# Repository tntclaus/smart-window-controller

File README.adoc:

# Контроллер умного окна

[.float-group]
--
image::docs/3d.png[float=left,width=200pt]

Устройство для управления рулонной шторой. Умеет:

1. Прятаться внутри трубы рулонной шторы. Ставится с другого конца от механической крутилки и имеет такой же габарит. Механическая крутилка сохраняется т.к. вручную шторами тоже удобно управлять.
2. Двигать шторой, в том числе зеброй.
3. Датчиком освещенности следить, чтобы шторы пропускали необходимое количество света.может делиться этой инфой с другими шторами.
4. Датчиком холла контролить текущее положение шторы, даже если шторой управляют вручную через цепочку.
5. Автокалибровать положения полностью свернутой шторы концевиком если пропало электричество и штору двигали вручную.
6. Общаться с дополнительной переферией по i2c / uart (если есть).
7. Опрашивать датчик открытого окна (если есть).
--

## Печатные платы

Дизайн в kicad. Печатная плата распаивается непосредственно на двигатель.

[.float-group]
--
image::docs/top.png[float=left,width=300pt]
image::docs/bottom.png[float=left,width=300pt]
--

## Корпус и другие детали

Печатается на 3D принтере. Дизайн в openscad. Часть деталей предназначена для стыковки вала двигателя с трубой
для рулонных штор ø32мм, остальная часть — для крепления двигателя и печатной платы к окну/стене/раме.

Список деталей:

. Чехол для стыковки вала и трубы 32мм;
. Корпус контроллера с хомутным соединением с корпусом двигателя и винтовым с печатной платой;
. Кронштейн для крепления к окну конца трубы с двигателем;
. Звездочка для шариковой цепи с креплением к 32мм трубе;
. Кронштейн для крепления к окну конца трубы со звездочкой.

## Покупные компоненты

. Ткань для рулонной шторы;
. Труба для рулонных штор ø32мм;
. Двигатель с редуктором JGA25-370;
. Блок питания AC 220 -> 12V для питания двигателя;
. Полномостовой драйвер A4950;
. DC-DC преобразователь 5-25V -> 3.3V;
. ESP8266-12E / ESP8266-12F;
. (опция) SMD или DIP фоторезистор (LDR) — для них на плате предусмотрено 2 места. Можно сделать выносным.
. (опция) концевой выключатель — подключается через JST-PH (2мм шаг) разъём. Open drain.
. (опция) датчик открытия окна — подключается через JST-PH (2мм шаг) разъём. Open drain.
. (опция) I2C периферия — подключается через JST-EH (2.5мм шаг) разъём. Питание 3.3В.
. (опция) UART периферия — подключается через JST-EH (2.5мм шаг) разъём программирования. Питание нужно брать от разъёма I2C.

## Выбор двигателя

На 100-200 оборотов в минуту. Большее число оборотов теоретически может не дать нужного крутящего момента, меньшее число оборотов может сделать ручное раскручивание шторы проблематичным. Крутящий момент при 100 оборотах в минуту у большинства двигателей будет порядка 1 кг для барабана шторы с радиусом 2 см.

## Прошивка

Открытая прошивка ESPHome. Плата имеет разъёмы для загрузки собственной прошивки.

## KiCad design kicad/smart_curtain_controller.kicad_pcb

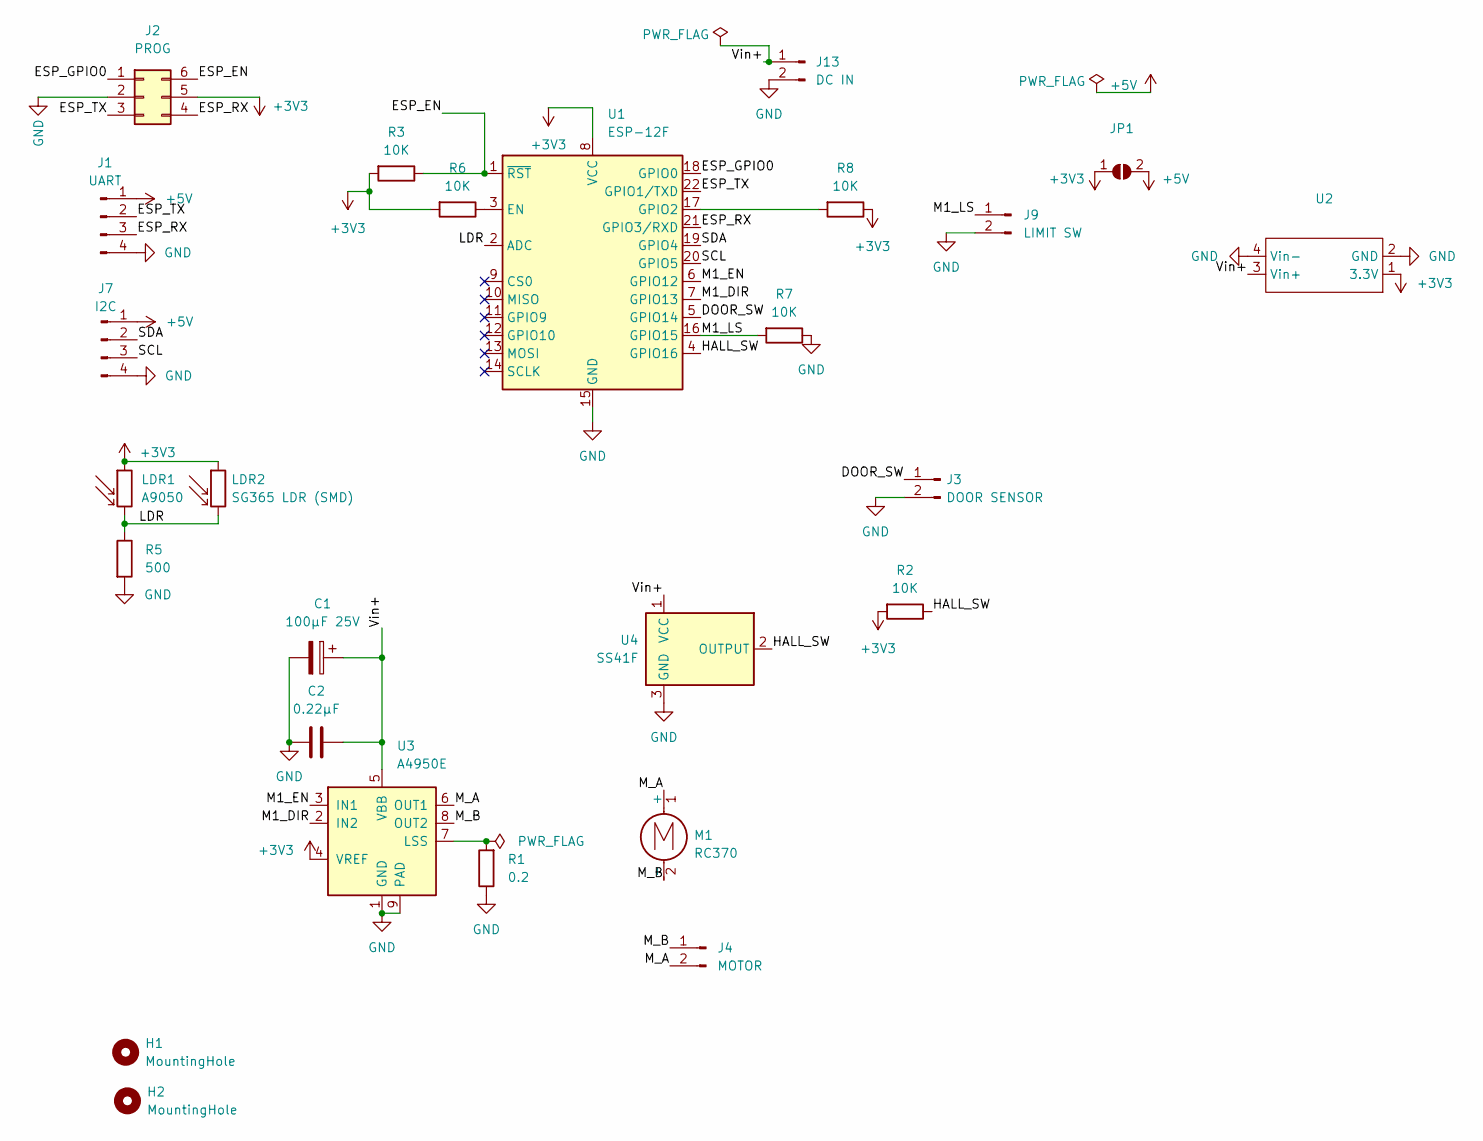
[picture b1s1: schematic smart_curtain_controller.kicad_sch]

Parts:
C1: 100µF 25V; CP_Radial_D6.3mm_P2.50mm
C2: 0.22µF; C_1206_3216Metric
H1, H2: MountingHole; MountingHole_3.2mm_M3
J1: UART; JST_PH_S4B-PH-K_1x04_P2.00mm_Horizontal
J2: PROG; PinHeader_2x03_P2.54mm_Vertical
J3: DOOR SENSOR; JST_PH_S2B-PH-K_1x02_P2.00mm_Horizontal
J4: MOTOR; JST_PH_S2B-PH-K_1x02_P2.00mm_Horizontal
J7: I2C; JST_PH_S4B-PH-K_1x04_P2.00mm_Horizontal
J9: LIMIT SW; JST_PH_S2B-PH-K_1x02_P2.00mm_Horizontal
J13: DC IN; JST_PH_S2B-PH-K_1x02_P2.00mm_Horizontal
JP1: (no value)
LDR1: A9050; R_LDR_5.0x4.1mm_P3mm_Vertical
LDR2: SG365 LDR (SMD); R_1210_3225Metric
M1: RC370
R1: 0.2; R_1206_3216Metric
R2, R3, R6, R7, R8: 10K; R_1206_3216Metric
R5: 500; R_1206_3216Metric
U1: ESP-12F; ESP-12E
U2: (no value)
U3: A4950E; SOIC-8-1EP_3.9x4.9mm_P1.27mm_EP2.41x3.3mm
U4: SS41F; Hall_Switch_TO-92

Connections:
+3V3: J2.5, JP1.1 (A), LDR1.1, LDR2.1, R2.2, R3.2, R6.2, R8.1, U1.8 (VCC), U2.1 (3.3V), U3.4 (VREF)
+5V: J1.1, J7.1, JP1.2 (B)
/DOOR_SW: J3.1, U1.5 (GPIO14)
/ESP_EN: J2.6, R3.1, U1.1 (~RST)
/ESP_GPIO0: J2.1, U1.18 (GPIO0)
/ESP_RX: J1.3, J2.4, U1.21 (GPIO3/RXD)
/ESP_TX: J1.2, J2.3, U1.22 (GPIO1/TXD)
/HALL_SW: R2.1, U1.4 (GPIO16), U4.2 (OUTPUT)
/LDR: LDR1.2, LDR2.2, R5.1, U1.2 (ADC)
/M1_DIR: U1.7 (GPIO13), U3.2 (IN2)
/M1_EN: U1.6 (GPIO12), U3.3 (IN1)
/M1_LS: J9.1, R7.2, U1.16 (GPIO15)
/M_A: J4.2, M1.1 (+), U3.6 (OUT1)
/M_B: J4.1, M1.2 (-), U3.8 (OUT2)
/SCL: J7.3, U1.20 (GPIO5)
/SDA: J7.2, U1.19 (GPIO4)
/Vin+: C1.1, C2.2, J13.1, U2.3 (Vin+), U3.5 (VBB), U4.1 (VCC)
GND: C1.2, C2.1, J1.4, J2.2, J3.2, J7.4, J9.2, J13.2, R1.1, R5.2, R7.1, U1.15 (GND), U2.2 (GND), U2.4 (Vin-), U3.1 (GND), U3.9 (PAD), U4.3 (GND)
unnamed: R1.2, U3.7 (LSS)
unnamed: R6.1, U1.3 (EN)
unnamed: R8.2, U1.17 (GPIO2)

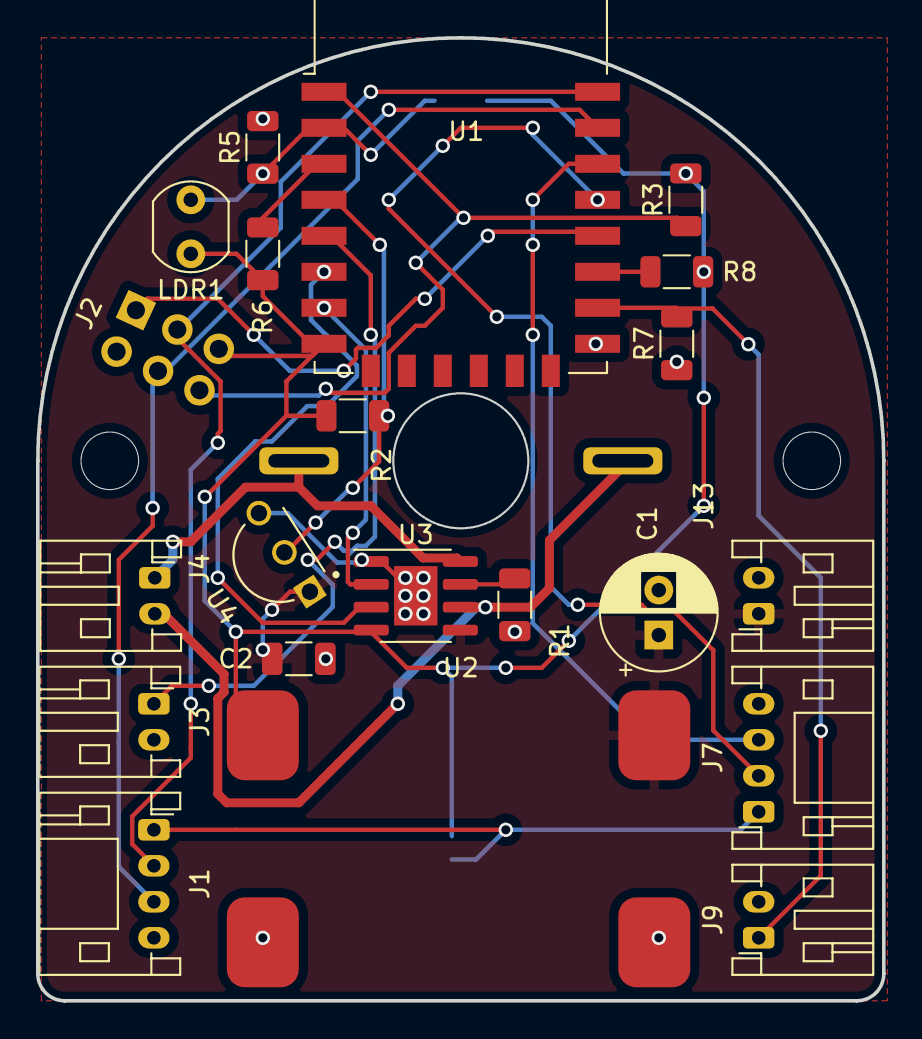
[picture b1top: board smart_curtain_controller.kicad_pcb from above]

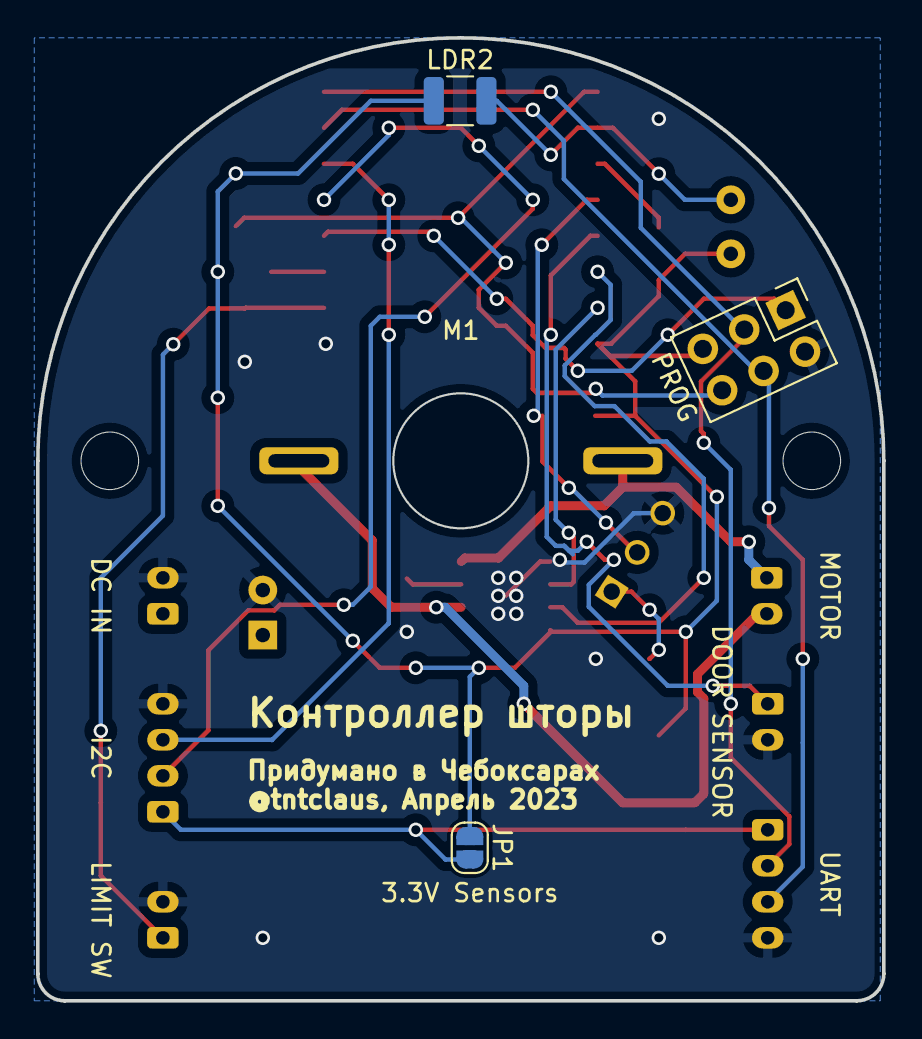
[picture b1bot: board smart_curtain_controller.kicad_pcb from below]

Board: 2 copper layers, 47.0 x 53.5 mm, 26 parts (4 on the bottom side), 21 nets.

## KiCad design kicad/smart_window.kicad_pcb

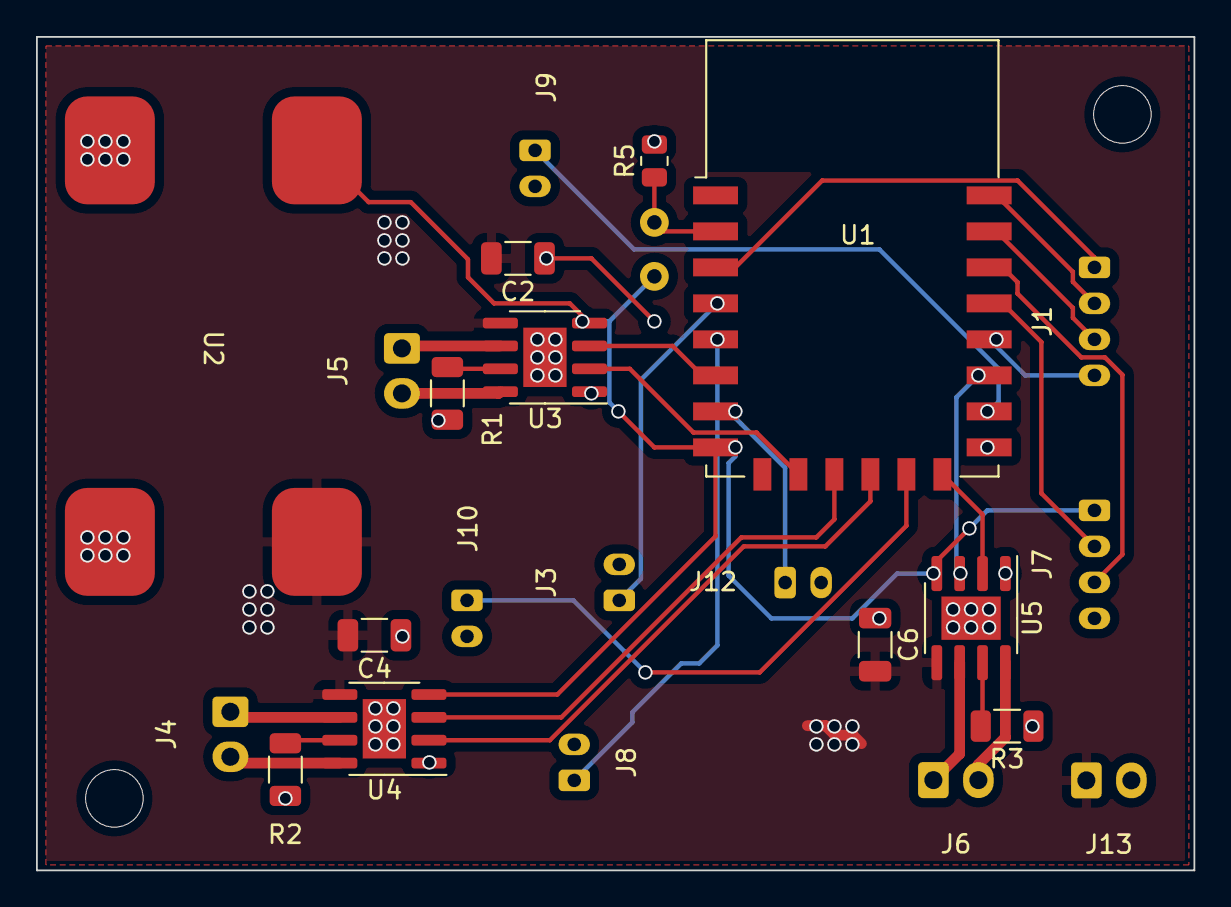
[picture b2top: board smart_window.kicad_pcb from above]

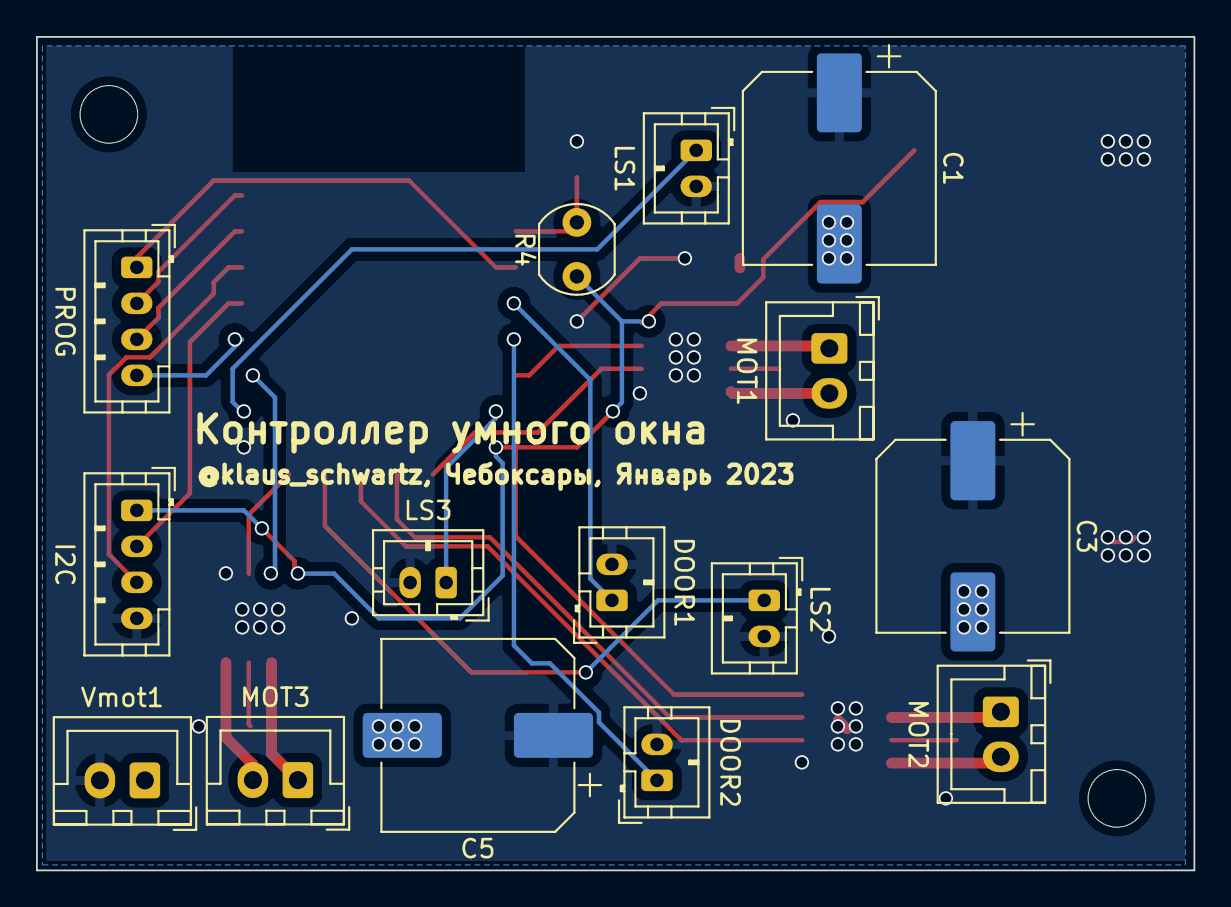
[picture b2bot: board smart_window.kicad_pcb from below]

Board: 2 copper layers, 64.3 x 46.3 mm, 29 parts (15 on the bottom side), 30 nets.

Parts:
C1, C3, C5: 100µF; CP_Elec_10x10.5
C2, C4, C6: 0.22µF; C_1206_3216Metric
H1, H2: MountingHole; MountingHole_3.2mm_M3
J1: PROG; JST_PH_B4B-PH-K_1x04_P2.00mm_Vertical
J3: DOOR1; JST_PH_B2B-PH-K_1x02_P2.00mm_Vertical
J4: MOT2; JST_XH_B2B-XH-A_1x02_P2.50mm_Vertical
J5: MOT1; JST_XH_B2B-XH-A_1x02_P2.50mm_Vertical
J6: MOT3; JST_XH_B2B-XH-A_1x02_P2.50mm_Vertical
J7: I2C; JST_PH_B4B-PH-K_1x04_P2.00mm_Vertical
J8: DOOR2; JST_PH_B2B-PH-K_1x02_P2.00mm_Vertical
J9: LS1; JST_PH_B2B-PH-K_1x02_P2.00mm_Vertical
J10: LS2; JST_PH_B2B-PH-K_1x02_P2.00mm_Vertical
J12: LS3; JST_PH_B2B-PH-K_1x02_P2.00mm_Vertical
J13: Vmot1; JST_XH_B2B-XH-A_1x02_P2.50mm_Vertical
R1, R2, R3: 0.2; R_1206_3216Metric
R4: A9050; R_LDR_5.0x4.1mm_P3mm_Vertical
R5: 500; R_0805_2012Metric
U1: ESP-12F; ESP-12E
U2: MP1584EN 3.3V; MP1584EN
U3, U4, U5: A4950E; SOIC-8-1EP_3.9x4.9mm_P1.27mm_EP2.41x3.3mm

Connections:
+3V3: J7.1, R4.1, U1.8 (VCC), U2.1 (3.3V), U3.4 (VREF), U4.4 (VREF), U5.4 (VREF)
/24V+: C1.2, C2.2, C3.2, C4.2, C5.2, C6.2, J13.1, U2.3 (Vin+), U3.5 (VBB), U4.5 (VBB), U5.5 (VBB)
/DOOR1: J3.1, U1.4 (GPIO16)
/DOOR2: J8.1, U1.5 (GPIO14)
/ESP_EN: J1.1, U1.3 (EN)
/ESP_GPIO0: J1.4, U1.18 (GPIO0)
/ESP_RX: J1.3, U1.21 (GPIO3/RXD)
/ESP_TX: J1.2, U1.22 (GPIO1/TXD)
/LDR: R4.2, R5.1, U1.2 (ADC)
/M1_DIR: U1.10 (MISO), U3.2 (IN2)
/M1_EN: U1.6 (GPIO12), U3.3 (IN1)
/M1_LS: J9.1, U1.16 (GPIO15)
/M2_DIR: U1.12 (GPIO10), U4.2 (IN2)
/M2_EN: U1.11 (GPIO9), U4.3 (IN1)
/M2_LS: J10.1, U1.13 (MOSI)
/M3_DIR: U1.14 (SCLK), U5.2 (IN2)
/M3_EN: U1.17 (GPIO2), U5.3 (IN1)
/M3_LS: J12.1, U1.7 (GPIO13)
/SCL: J7.3, U1.20 (GPIO5)
/SDA: J7.2, U1.19 (GPIO4)
GND: C1.1, C2.1, C3.1, C4.1, C5.1, C6.1, J3.2, J7.4, J8.2, J9.2, J10.2, J12.2, J13.2, R1.1, R2.1, R3.1, R5.2, U1.15 (GND), U2.2 (GND), U2.4 (Vin-), U3.1 (GND), U3.9 (PAD), U4.1 (GND), U4.9 (PAD), U5.1 (GND), U5.9 (PAD)
unnamed: J4.1, U4.6 (OUT1)
unnamed: J4.2, U4.8 (OUT2)
unnamed: J5.1, U3.6 (OUT1)
unnamed: J5.2, U3.8 (OUT2)
unnamed: J6.1, U5.6 (OUT1)
unnamed: J6.2, U5.8 (OUT2)
unnamed: R1.2, U3.7 (LSS)
unnamed: R2.2, U4.7 (LSS)
unnamed: R3.2, U5.7 (LSS)

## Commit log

2023-01-01 Первая версия
2023-01-01 rename readme
2023-01-01 Create LICENSE
2023-01-01 добавил фотосенсор
2023-01-01 добавлен DC-DC преобразователь для питания 3В от БП двигателя
2023-01-19 версия с мостами на биполярных транзисторах
2023-01-20 вариант с микросхемами a4950
2023-01-20 изменено положение монтажных отверстий
2023-01-23 2-сторонняя версия
2023-04-22 simple version that should work
